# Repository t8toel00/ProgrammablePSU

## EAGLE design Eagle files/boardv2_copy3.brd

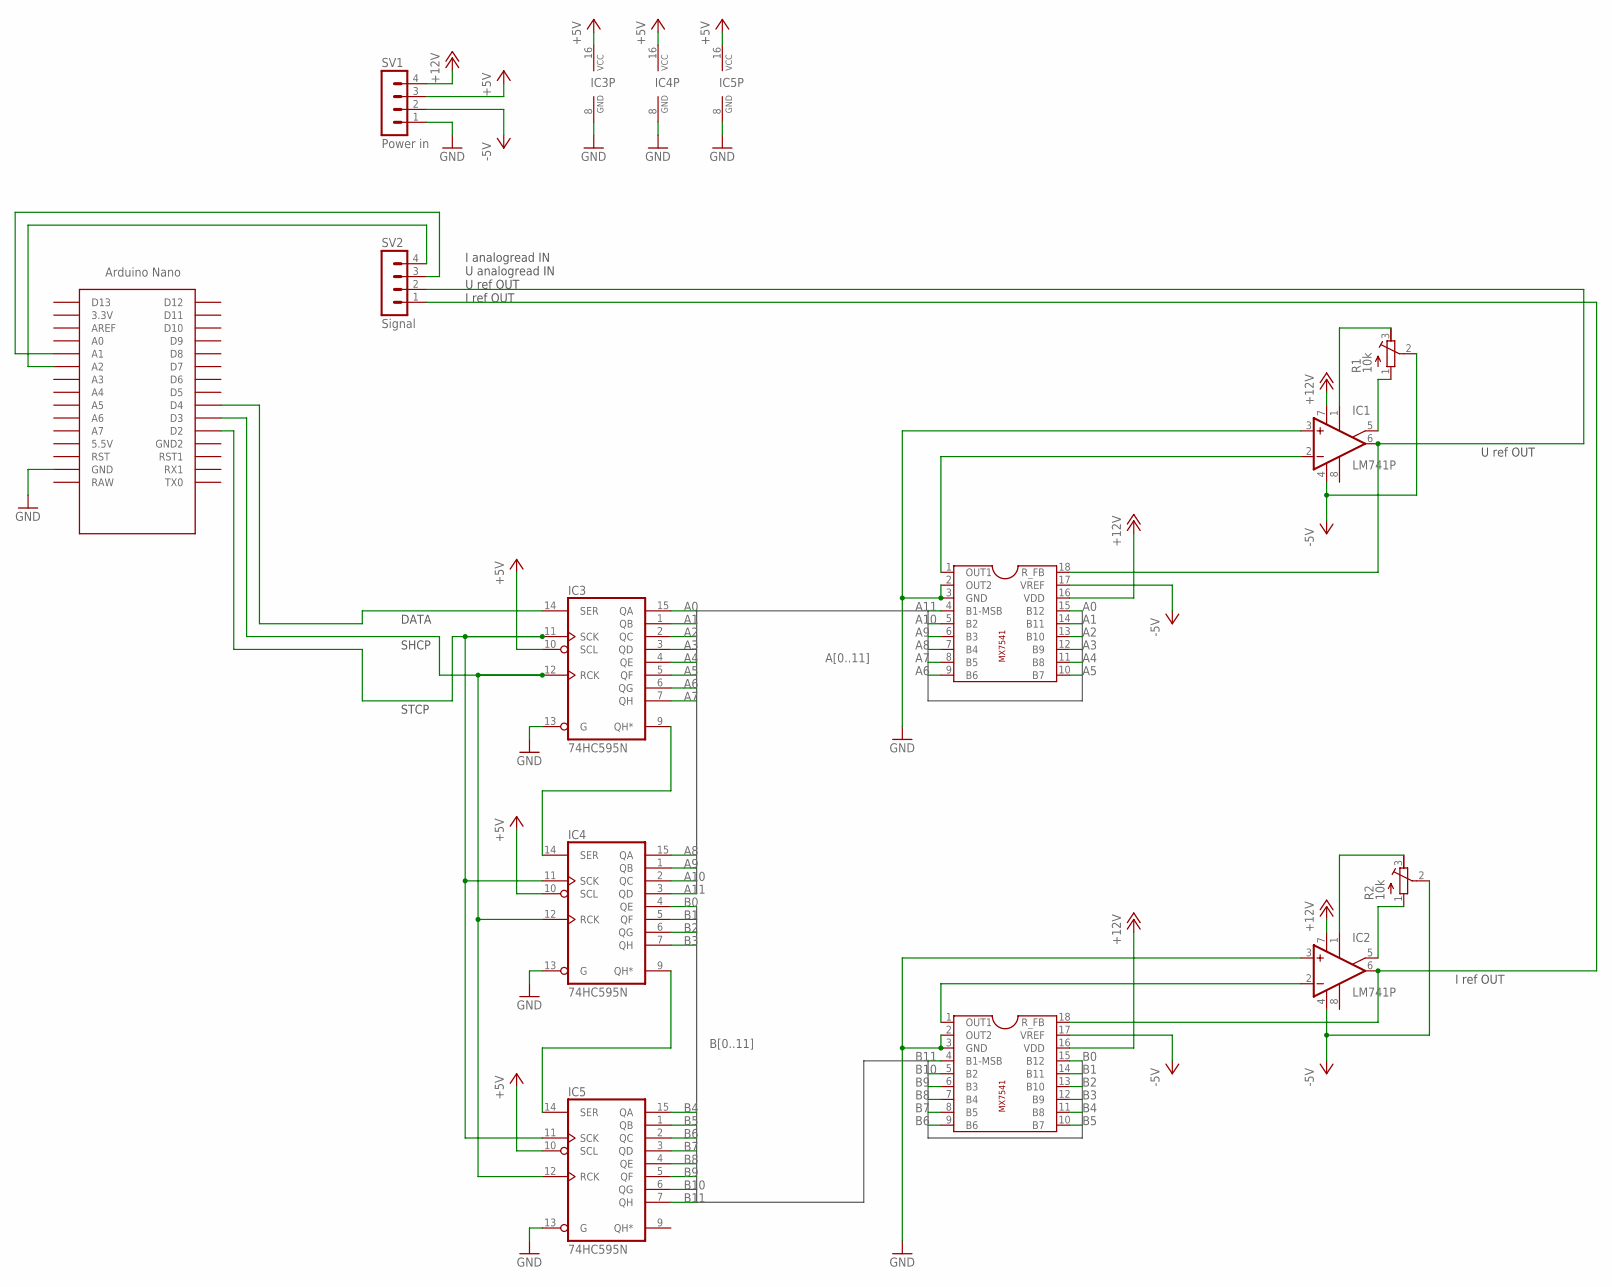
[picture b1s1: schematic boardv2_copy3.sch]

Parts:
IC1, IC2: LM741P; DIL08
IC3, IC4, IC5: 74HC595N; DIL16
R1, R2: 10k; RTRIM64W
SV1: Power in; MA04-1
SV2: Signal; MA04-1
U$1, U$2: MX7541
U$3: NANO

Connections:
+5V: IC3.10 (SCL), IC3.16 (VCC), IC4.10 (SCL), IC4.16 (VCC), IC5.10 (SCL), IC5.16 (VCC), SV1.3
+12V: IC1.7 (V+), IC2.7 (V+), SV1.4, U$1.16 (VDD), U$2.16 (VDD)
-5V: IC1.4 (V-), IC2.4 (V-), R1.2 (S), R2.2 (S), SV1.2, U$1.17 (VREF), U$2.17 (VREF)
A0: IC3.15 (QA), U$1.15 (B12)
A1: IC3.1 (QB), U$1.14 (B11)
A2: IC3.2 (QC), U$1.13 (B10)
A3: IC3.3 (QD), U$1.12 (B9)
A4: IC3.4 (QE), U$1.11 (B8)
A5: IC3.5 (QF), U$1.10 (B7)
A6: IC3.6 (QG), U$1.9 (B6)
A7: IC3.7 (QH), U$1.8 (B5)
A8: IC4.15 (QA), U$1.7 (B4)
A9: IC4.1 (QB), U$1.6 (B3)
A10: IC4.2 (QC), U$1.5 (B2)
A11: IC4.3 (QD), U$1.4 (B1-MSB)
B0: IC4.4 (QE), U$2.15 (B12)
B1: IC4.5 (QF), U$2.14 (B11)
B2: IC4.6 (QG), U$2.13 (B10)
B3: IC4.7 (QH), U$2.12 (B9)
B4: IC5.15 (QA), U$2.11 (B8)
B5: IC5.1 (QB), U$2.10 (B7)
B6: IC5.2 (QC), U$2.9 (B6)
B7: IC5.3 (QD), U$2.8 (B5)
B8: IC5.4 (QE), U$2.7 (B4)
B9: IC5.5 (QF), U$2.6 (B3)
B10: IC5.6 (QG), U$2.5 (B2)
B11: IC5.7 (QH), U$2.4 (B1-MSB)
GND: IC1.3 (+IN), IC2.3 (+IN), IC3.8 (GND), IC3.13 (G), IC4.8 (GND), IC4.13 (G), IC5.8 (GND), IC5.13 (G), SV1.1, U$1.2 (OUT2), U$1.3 (GND), U$2.2 (OUT2), U$2.3 (GND), U$3.GND
unnamed: IC3.9 (QH*), IC4.14 (SER)
unnamed: IC4.9 (QH*), IC5.14 (SER)
unnamed: IC3.11 (SCK), IC4.11 (SCK), IC5.11 (SCK), U$3.D2
unnamed: IC3.12 (RCK), IC4.12 (RCK), IC5.12 (RCK), U$3.D3
unnamed: IC3.14 (SER), U$3.D4
unnamed: SV2.4, U$3.A2
unnamed: SV2.3, U$3.A1
unnamed: IC1.2 (-IN), U$1.1 (OUT1)
unnamed: IC2.2 (-IN), U$2.1 (OUT1)
unnamed: IC1.1 (ON1), R1.3 (E)
unnamed: IC1.5 (ON2), R1.1 (A)
unnamed: IC2.1 (ON1), R2.3 (E)
unnamed: IC2.5 (ON2), R2.1 (A)
unnamed: IC1.6 (OUT), SV2.2, U$1.18 (R_FB)
unnamed: IC2.6 (OUT), SV2.1, U$2.18 (R_FB)

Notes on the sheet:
SHCP
STCP
DATA
U ref OUT
I ref OUT
I analogread IN U analogread IN U ref OUT I ref OUT

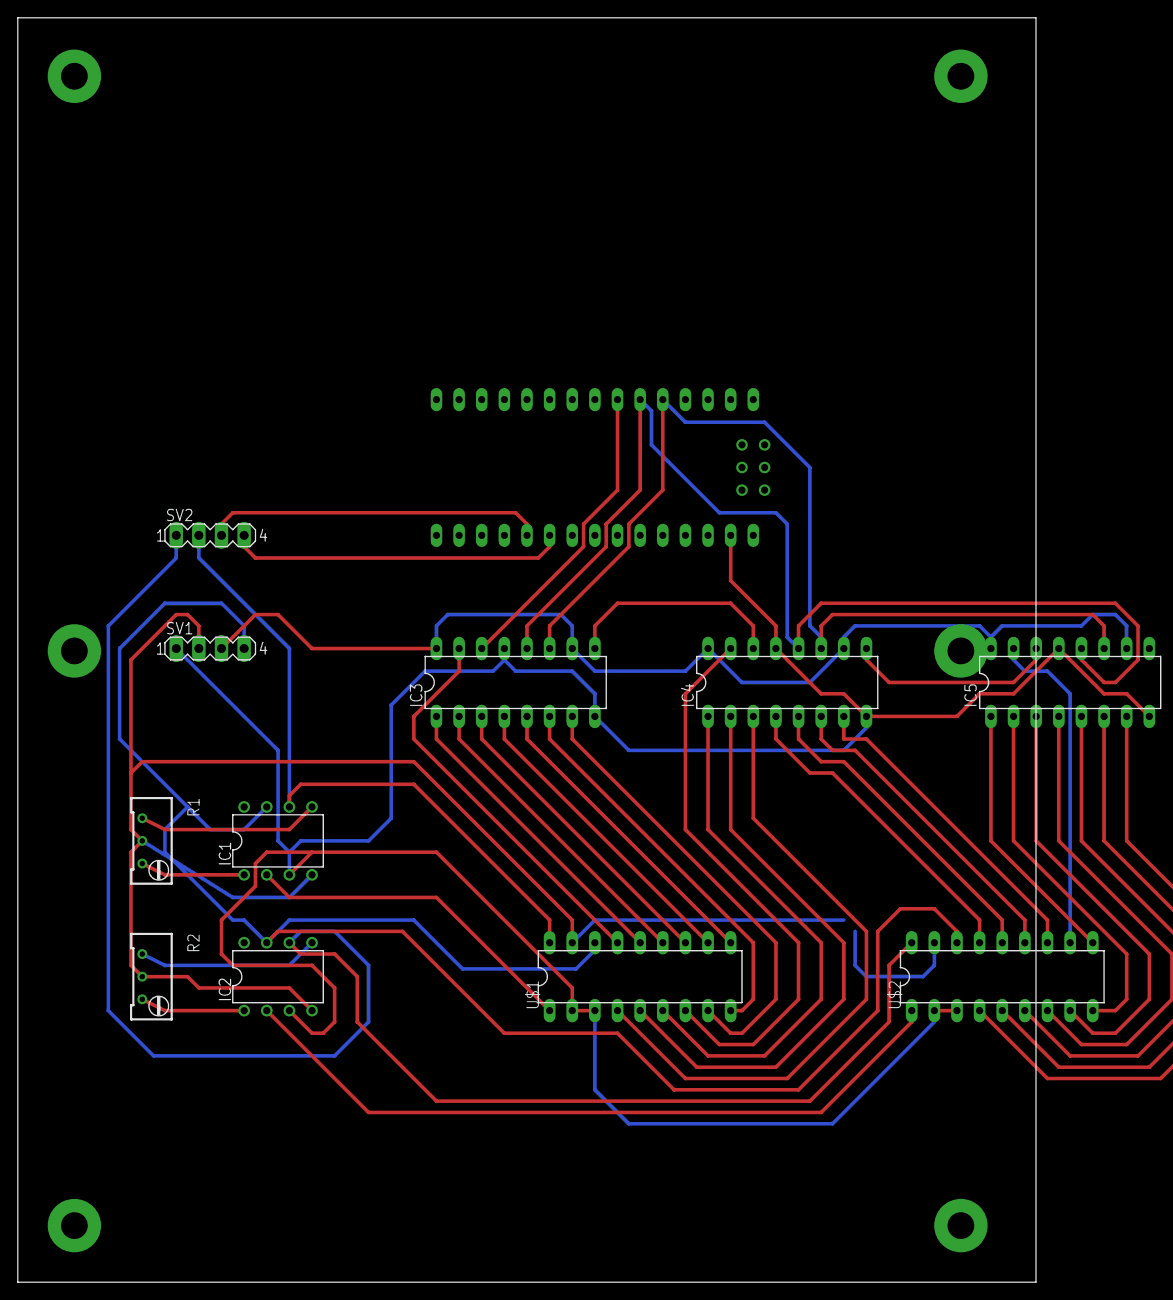
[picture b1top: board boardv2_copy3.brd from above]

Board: 2 copper layers, 114.3 x 141.9 mm, 12 parts (0 on the bottom side), 43 nets.

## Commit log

2019-12-24 Added files
